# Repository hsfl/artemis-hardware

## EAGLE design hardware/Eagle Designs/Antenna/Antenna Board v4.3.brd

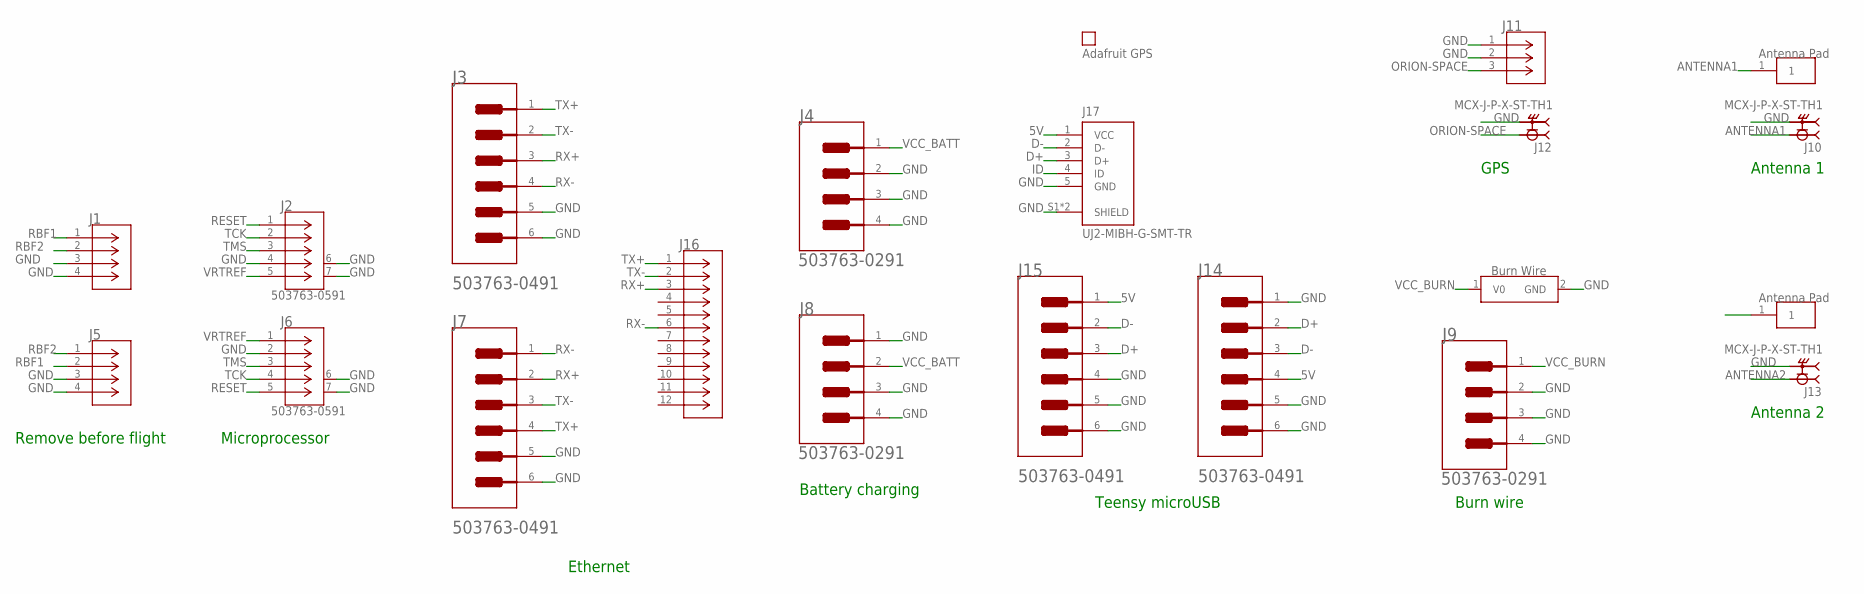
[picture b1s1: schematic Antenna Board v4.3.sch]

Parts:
GPS: PA1010D
J1, J5: 5037630291; CON_5037630291
J2, J6: 503763-0591; CONN_5037630591_MOL
J3, J7, J14, J15: MOLEX_503763-0491MOLEX_503763-0491_0_0; MOLEX_503763-0491_0
J4, J8, J9: MOLEX_503763-0291MOLEX_503763-0291_0_0; MOLEX_503763-0291_0
J10, J12, J13: MCX-J-P-X-ST-TH1; SAMTEC_MCX-J-P-X-ST-TH1
J11: U.FL-R-SMT-1(01); CONN_-SMT-1(01)
J16: ARJM11C7-104-AB-EW2; CONN_EW_ABR
J17: UJ2-MIBH-G-SMT-TR; CUI_UJ2-MIBH-G-SMT-TR
U$1, U$2: ANTENNA_PAD+HOLES
U$3: BURNWIRE

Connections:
5V: J14.4, J15.1, J17.1 (VCC)
ANTENNA1: J10.1, U$1.1
ANTENNA2: J13.1, U$2.1
D+: J14.2, J15.3, J17.3 (D+)
D-: J14.3, J15.2, J17.2 (D-)
GND: J1.3, J1.4, J2.4, J2.6, J2.7, J3.5 (MNT_1), J3.6 (MNT_2), J4.2, J4.3 (MNT_1), J4.4 (MNT_2), J5.3, J5.4, J6.2, J6.6, J6.7, J7.5 (MNT_1), J7.6 (MNT_2), J8.1, J8.3 (MNT_1), J8.4 (MNT_2), J9.2, J9.3 (MNT_1), J9.4 (MNT_2), J10.S1 (2), J10.S2 (2), J10.S3 (2), J10.S4 (2), J11.1, J11.2, J12.S1 (2), J12.S2 (2), J12.S3 (2), J12.S4 (2), J13.S1 (2), J13.S2 (2), J13.S3 (2), J13.S4 (2), J14.1, J14.5 (MNT_1), J14.6 (MNT_2), J15.4, J15.5 (MNT_1), J15.6 (MNT_2), J17.5 (GND), J17.S1 (SHIELD), J17.S2 (SHIELD), U$3.2 (GND)
ID: J17.4 (ID)
ORION-SPACE: J11.3, J12.1
RBF1: J1.1, J5.2
RBF2: J1.2, J5.1
RESET: J2.1, J6.5
RX+: J3.3, J7.2, J16.3
RX-: J3.4, J7.1, J16.6
TCK: J2.2, J6.4
TMS: J2.3, J6.3
TX+: J3.1, J7.4, J16.1
TX-: J3.2, J7.3, J16.2
VCC_BATT: J4.1, J8.2
VCC_BURN: J9.1, U$3.1 (V0)
VRTREF: J2.5, J6.1

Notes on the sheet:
Remove before flight
Microprocessor
Battery charging
Teensy microUSB
Burn wire
GPS
Antenna 1
Antenna 2
Ethernet

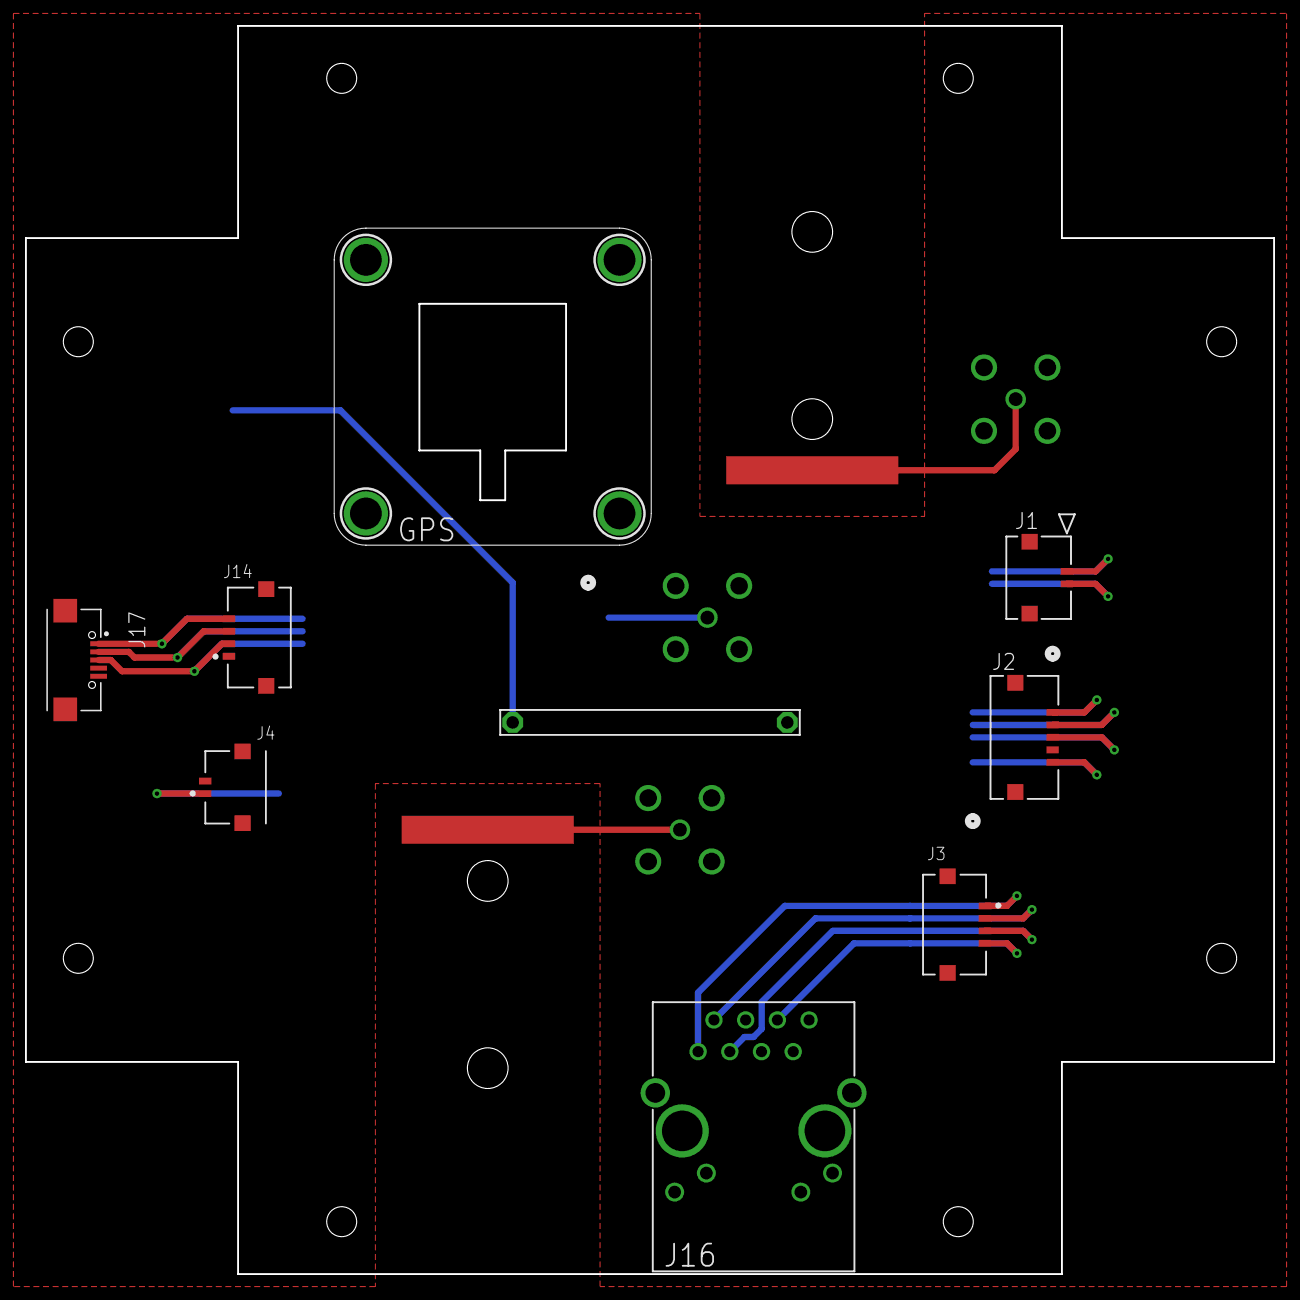
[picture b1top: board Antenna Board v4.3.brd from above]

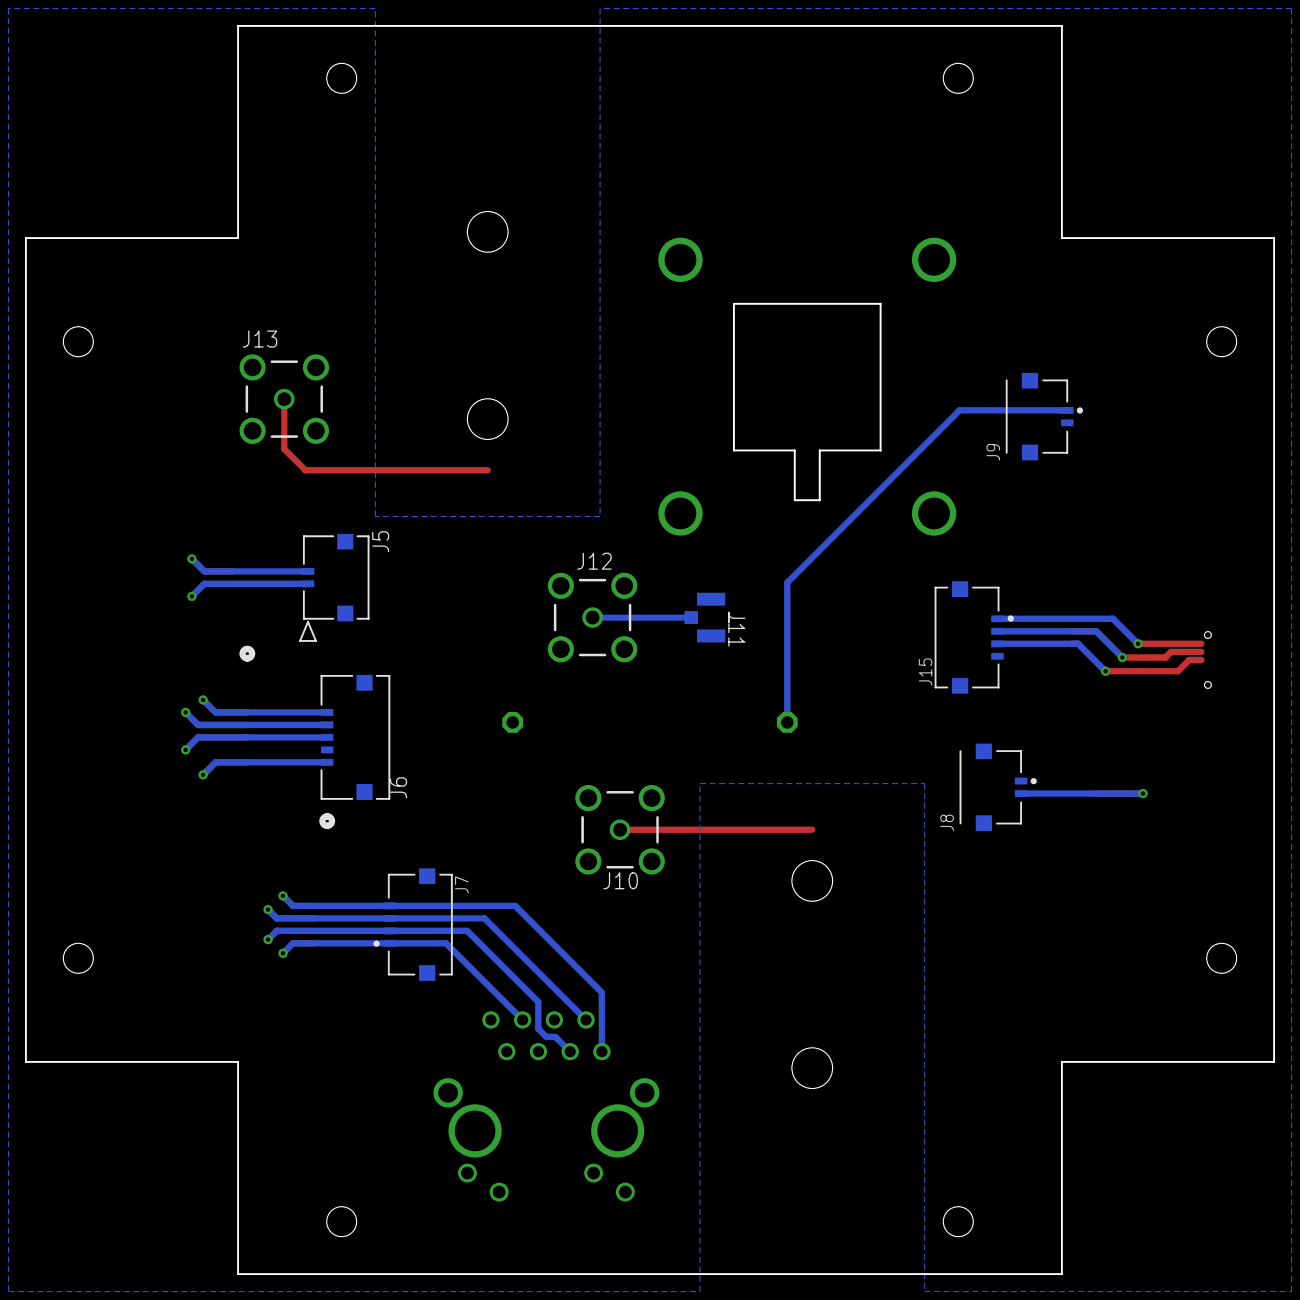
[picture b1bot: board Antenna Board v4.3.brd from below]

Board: 2 copper layers, 100.0 x 100.0 mm, 21 parts (10 on the bottom side), 19 nets.

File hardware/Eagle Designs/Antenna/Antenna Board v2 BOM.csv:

"Part";"Value";"Device";"Package";"Description";"AUTOMOTIVE";"BUILT_BY";"CENTROID_NOT_SPECIFIED";"CONN_GENDER";"CONN_ORIENTATION";"CONTACT_MATERIAL";"COPYRIGHT";"CURRENT_RATING";"DATASHEET";"DEVICE_CLASS_L1";"DEVICE_CLASS_L2";"DEVICE_CLASS_L3";"DIGIKEY_DESCRIPTION";"DIGIKEY_PART_NUMBER";"FOOTPRINT_URL";"FOOTPRINT_VARIANT_NAME_0";"HEIGHT";"LEAD_FREE";"MANUFACTURER_PART_NUMBER";"MF";"MFG_PACKAGE_IDENT";"MFG_PACKAGE_IDENT_DATE";"MFG_PACKAGE_IDENT_REV";"MOUSER_PART_NUMBER";"MPN";"NUMBER_OF_CONTACTS";"NUMBER_OF_ROWS";"PACKAGE";"PITCH";"PREFIX";"ROHS";"SOURCELIBRARY";"TEMPERATURE_RANGE_HIGH";"TEMPERATURE_RANGE_LOW";"VENDOR";"VERIFICATION_VERSION";"VOLTAGE_RATING";
"J1";"503763-0591";"503763-0591";"CONN_5037630591_MOL";"";"";"EMA_Cory";"";"";"";"";"Copyright (C) 2018 Accelerated Designs. All rights reserved";"";"https://www.molex.com/pdm_docs/sd/5037630591_sd.pdf";"";"";"";"";"";"";"";"";"";"503763-0591";"";"";"";"";"";"";"";"";"";"";"";"";"Add_to_database_2020-12-14";"";"";"Molex Connector Corporation";"";"";
"J2";"MOLEX_503763-0491MOLEX_503763-0491_0_0";"MOLEX_503763-0491MOLEX_503763-0491_0_0";"MOLEX_503763-0491_0";"Wire-To-Board Connector, Pico-Lock 503763 Series, Surface Mount, Header, 4 Contacts, 1 mm";"No";"";"No";"Male";"Right Angle";"Gold,Nickel";"";"1.5A";"https://www.molex.com/webdocs/datasheets/pdf/en-us/503763049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";"Connectors";"Headers and Wire Housings";"unset";"CONN HEADER 1MM R/A 4CKT";"WM10655CT-ND";"https://www.molex.com/pdm_docs/sd/5037630491_sd.pdf";"Recommended_Land_Pattern";"1.7mm";"Yes";"";"Molex";"503763-0491";"0";"0";"538-503763-0491";"503763-0491";"4";"1";"HDR4";"1mm";"J";"Yes";"";"+105°C";"-40°C";"";"0.0.0.1";"150V";
"J3";"MOLEX_503763-0491MOLEX_503763-0491_0_0";"MOLEX_503763-0491MOLEX_503763-0491_0_0";"MOLEX_503763-0491_0";"Wire-To-Board Connector, Pico-Lock 503763 Series, Surface Mount, Header, 4 Contacts, 1 mm";"No";"";"No";"Male";"Right Angle";"Gold,Nickel";"";"1.5A";"https://www.molex.com/webdocs/datasheets/pdf/en-us/503763049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";"Connectors";"Headers and Wire Housings";"unset";"CONN HEADER 1MM R/A 4CKT";"WM10655CT-ND";"https://www.molex.com/pdm_docs/sd/5037630491_sd.pdf";"Recommended_Land_Pattern";"1.7mm";"Yes";"";"Molex";"503763-0491";"0";"0";"538-503763-0491";"503763-0491";"4";"1";"HDR4";"1mm";"J";"Yes";"";"+105°C";"-40°C";"";"0.0.0.1";"150V";
"J4";"MOLEX_503763-0291MOLEX_503763-0291_0_0";"MOLEX_503763-0291MOLEX_503763-0291_0_0";"MOLEX_503763-0291_0";"2 Positions Header Connector 0.039" (1.00mm) Surface Mount, Right Angle Gold";"";"";"No";"";"";"";"";"";"http://www.molex.com/pdm_docs/sd/5037630291_sd.pdf";"";"";"";"CONN HEADER 1MM R/A 2CKT";"WM10654CT-ND";"";"";"";"yes";"";"Molex";"";"";"";"538-503763-0291";"503763-0291";"";"";"HDR02";"";"J";"yes";"";"+105°C";"-40°C";"";"";"";
"J5";"503763-0591";"503763-0591";"CONN_5037630591_MOL";"";"";"EMA_Cory";"";"";"";"";"Copyright (C) 2018 Accelerated Designs. All rights reserved";"";"https://www.molex.com/pdm_docs/sd/5037630591_sd.pdf";"";"";"";"";"";"";"";"";"";"503763-0591";"";"";"";"";"";"";"";"";"";"";"";"";"Add_to_database_2020-12-14";"";"";"Molex Connector Corporation";"";"";
"J6";"MOLEX_503763-0491MOLEX_503763-0491_0_0";"MOLEX_503763-0491MOLEX_503763-0491_0_0";"MOLEX_503763-0491_0";"Wire-To-Board Connector, Pico-Lock 503763 Series, Surface Mount, Header, 4 Contacts, 1 mm";"No";"";"No";"Male";"Right Angle";"Gold,Nickel";"";"1.5A";"https://www.molex.com/webdocs/datasheets/pdf/en-us/503763049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";"Connectors";"Headers and Wire Housings";"unset";"CONN HEADER 1MM R/A 4CKT";"WM10655CT-ND";"https://www.molex.com/pdm_docs/sd/5037630491_sd.pdf";"Recommended_Land_Pattern";"1.7mm";"Yes";"";"Molex";"503763-0491";"0";"0";"538-503763-0491";"503763-0491";"4";"1";"HDR4";"1mm";"J";"Yes";"";"+105°C";"-40°C";"";"0.0.0.1";"150V";
"J7";"MOLEX_503763-0491MOLEX_503763-0491_0_0";"MOLEX_503763-0491MOLEX_503763-0491_0_0";"MOLEX_503763-0491_0";"Wire-To-Board Connector, Pico-Lock 503763 Series, Surface Mount, Header, 4 Contacts, 1 mm";"No";"";"No";"Male";"Right Angle";"Gold,Nickel";"";"1.5A";"https://www.molex.com/webdocs/datasheets/pdf/en-us/503763049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";"Connectors";"Headers and Wire Housings";"unset";"CONN HEADER 1MM R/A 4CKT";"WM10655CT-ND";"https://www.molex.com/pdm_docs/sd/5037630491_sd.pdf";"Recommended_Land_Pattern";"1.7mm";"Yes";"";"Molex";"503763-0491";"0";"0";"538-503763-0491";"503763-0491";"4";"1";"HDR4";"1mm";"J";"Yes";"";"+105°C";"-40°C";"";"0.0.0.1";"150V";
"J8";"MOLEX_503763-0291MOLEX_503763-0291_0_0";"MOLEX_503763-0291MOLEX_503763-0291_0_0";"MOLEX_503763-0291_0";"2 Positions Header Connector 0.039" (1.00mm) Surface Mount, Right Angle Gold";"";"";"No";"";"";"";"";"";"http://www.molex.com/pdm_docs/sd/5037630291_sd.pdf";"";"";"";"CONN HEADER 1MM R/A 2CKT";"WM10654CT-ND";"";"";"";"yes";"";"Molex";"";"";"";"538-503763-0291";"503763-0291";"";"";"HDR02";"";"J";"yes";"";"+105°C";"-40°C";"";"";"";
"J9";"MOLEX_503763-0291MOLEX_503763-0291_0_0";"MOLEX_503763-0291MOLEX_503763-0291_0_0";"MOLEX_503763-0291_0";"2 Positions Header Connector 0.039" (1.00mm) Surface Mount, Right Angle Gold";"";"";"No";"";"";"";"";"";"http://www.molex.com/pdm_docs/sd/5037630291_sd.pdf";"";"";"";"CONN HEADER 1MM R/A 2CKT";"WM10654CT-ND";"";"";"";"yes";"";"Molex";"";"";"";"538-503763-0291";"503763-0291";"";"";"HDR02";"";"J";"yes";"";"+105°C";"-40°C";"";"";"";
"J10";"U.FL-R-SMT-1(01)";"U.FL-R-SMT-1(01)";"CONN_-SMT-1(01)";"";"";"EMA_Matt";"";"";"";"";"Copyright (C) 2018 Accelerated Designs. All rights reserved";"";"";"";"";"";"";"";"";"";"";"";"U.FL-R-SMT-1(01)";"";"";"";"";"";"";"";"";"";"";"";"";"Hirose_12_20_2019";"";"";"Hirose";"";"";
"J11";"U.FL-R-SMT-1(01)";"U.FL-R-SMT-1(01)";"CONN_-SMT-1(01)";"";"";"EMA_Matt";"";"";"";"";"Copyright (C) 2018 Accelerated Designs. All rights reserved";"";"";"";"";"";"";"";"";"";"";"";"U.FL-R-SMT-1(01)";"";"";"";"";"";"";"";"";"";"";"";"";"Hirose_12_20_2019";"";"";"Hirose";"";"";
"J12";"U.FL-R-SMT-1(01)";"U.FL-R-SMT-1(01)";"CONN_-SMT-1(01)";"";"";"EMA_Matt";"";"";"";"";"Copyright (C) 2018 Accelerated Designs. All rights reserved";"";"";"";"";"";"";"";"";"";"";"";"U.FL-R-SMT-1(01)";"";"";"";"";"";"";"";"";"";"";"";"";"Hirose_12_20_2019";"";"";"Hirose";"";"";
"U$2";"ANTENNA_PAD";"ANTENNA_PAD";"ANTENNA_PAD";"";"";"";"";"";"";"";"";"";"";"";"";"";"";"";"";"";"";"";"";"";"";"";"";"";"";"";"";"";"";"";"";"";"";"";"";"";"";
"U$3";"BURNWIRE";"BURNWIRE";"BURNWIRE";"";"";"";"";"";"";"";"";"";"";"";"";"";"";"";"";"";"";"";"";"";"";"";"";"";"";"";"";"";"";"";"";"";"";"";"";"";"";

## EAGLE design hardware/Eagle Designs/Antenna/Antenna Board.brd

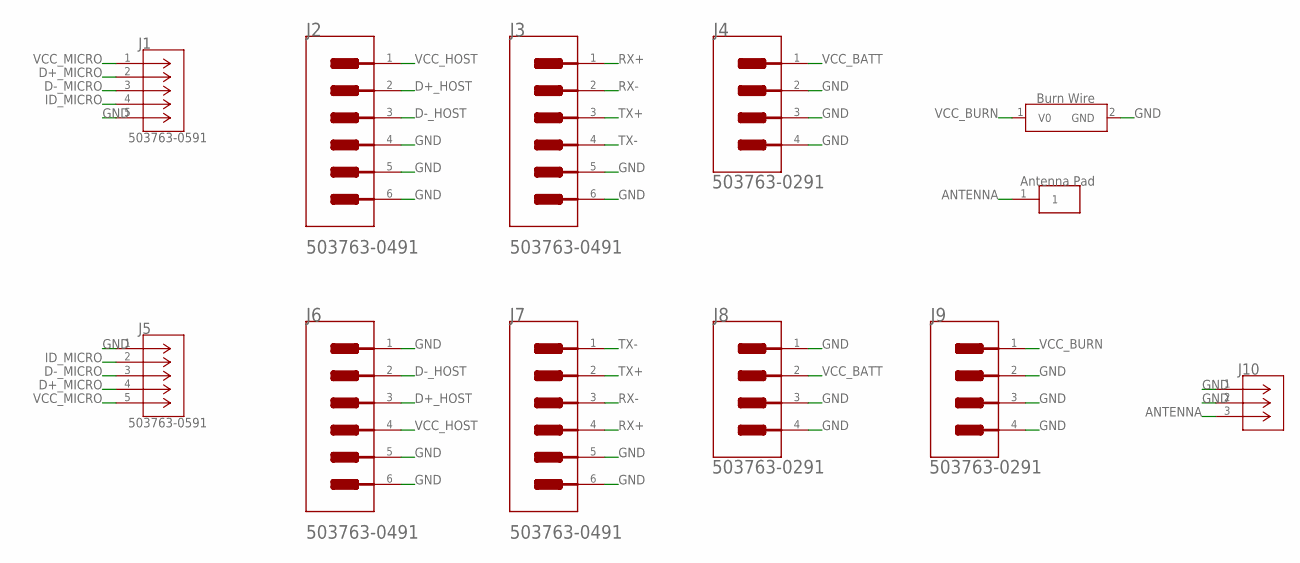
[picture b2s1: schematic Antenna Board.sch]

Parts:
J1, J5: 503763-0591; CONN_5037630591_MOL
J2, J3, J6, J7: MOLEX_503763-0491MOLEX_503763-0491_0_0; MOLEX_503763-0491_0
J4, J8, J9: MOLEX_503763-0291MOLEX_503763-0291_0_0; MOLEX_503763-0291_0
J10: U.FL-R-SMT-1(01); CONN_-SMT-1(01)
U$2: ANTENNA_PAD
U$3: BURNWIRE

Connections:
ANTENNA: J10.3, U$2.1
D+_HOST: J2.2, J6.3
D+_MICRO: J1.2, J5.4
D-_HOST: J2.3, J6.2
D-_MICRO: J1.3, J5.3
GND: J1.5, J2.4, J2.5 (MNT_1), J2.6 (MNT_2), J3.5 (MNT_1), J3.6 (MNT_2), J4.2, J4.3 (MNT_1), J4.4 (MNT_2), J5.1, J6.1, J6.5 (MNT_1), J6.6 (MNT_2), J7.5 (MNT_1), J7.6 (MNT_2), J8.1, J8.3 (MNT_1), J8.4 (MNT_2), J9.2, J9.3 (MNT_1), J9.4 (MNT_2), J10.1, J10.2, U$3.2 (GND)
ID_MICRO: J1.4, J5.2
RX+: J3.1, J7.4
RX-: J3.2, J7.3
TX+: J3.3, J7.2
TX-: J3.4, J7.1
VCC_BATT: J4.1, J8.2
VCC_BURN: J9.1, U$3.1 (V0)
VCC_HOST: J2.1, J6.4
VCC_MICRO: J1.1, J5.5

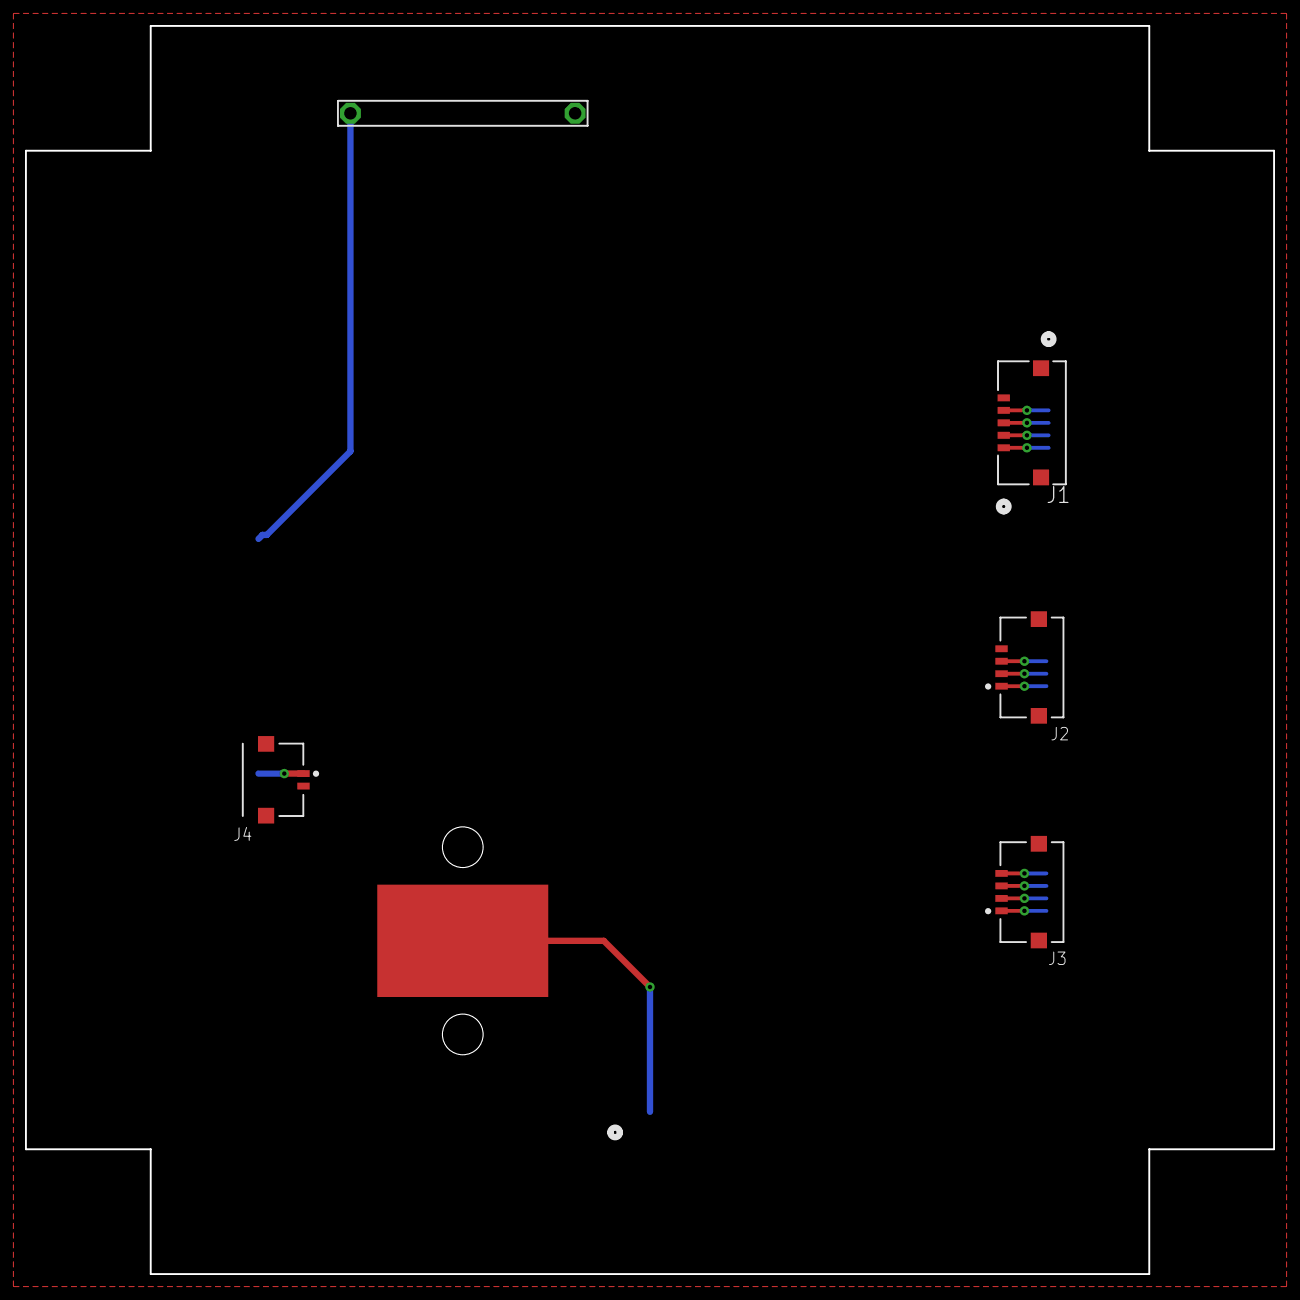
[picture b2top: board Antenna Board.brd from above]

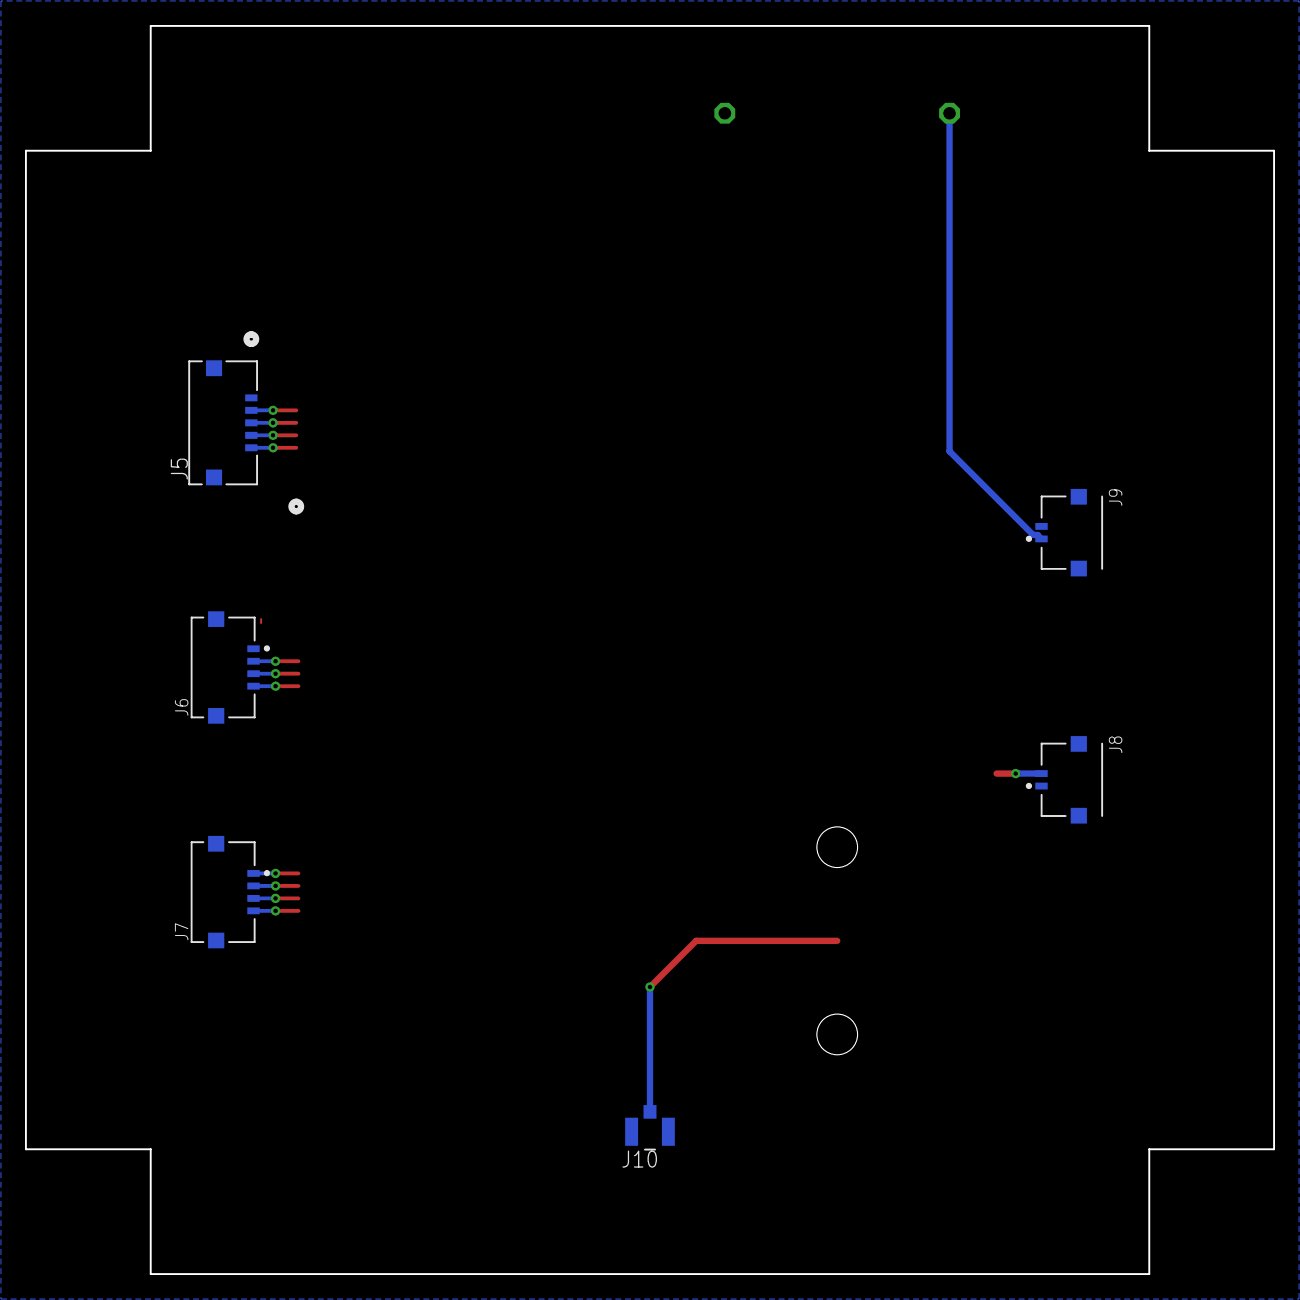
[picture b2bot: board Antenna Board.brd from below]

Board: 2 copper layers, 100.0 x 100.0 mm, 12 parts (6 on the bottom side), 15 nets.

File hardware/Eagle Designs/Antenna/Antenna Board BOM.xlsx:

Part | Value | Device | Package | Description
J1, J5 | 503763-0591 | 503763-0591 | CONN_5037630591_MOL
J2, J3, J6, J7 | 503763-0491 | MOLEX_503763-0491MOLEX_503763-0491_0_0 | MOLEX_503763-0491_0 | Wire-To-Board Connector, Pico-Lock 503763 Series, Surface Mount, Header, 4 Cont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
J4, J8, J9 | 503763-0291 | MOLEX_503763-0291MOLEX_503763-0291_0_0 | MOLEX_503763-0291_0 | 2 Positions Header Connector 0.039 (1.00mm) Surface Mount, Right Angle Gold"
J10 | U.FL-R-SMT-1(01) | U.FL-R-SMT-1(01) | CONN_-SMT-1(01)
U$2 | ANTENNA_PAD | ANTENNA_PAD | ANTENNA_PAD
U$3 | BURNWIRE | BURNWIRE | BURNWIRE

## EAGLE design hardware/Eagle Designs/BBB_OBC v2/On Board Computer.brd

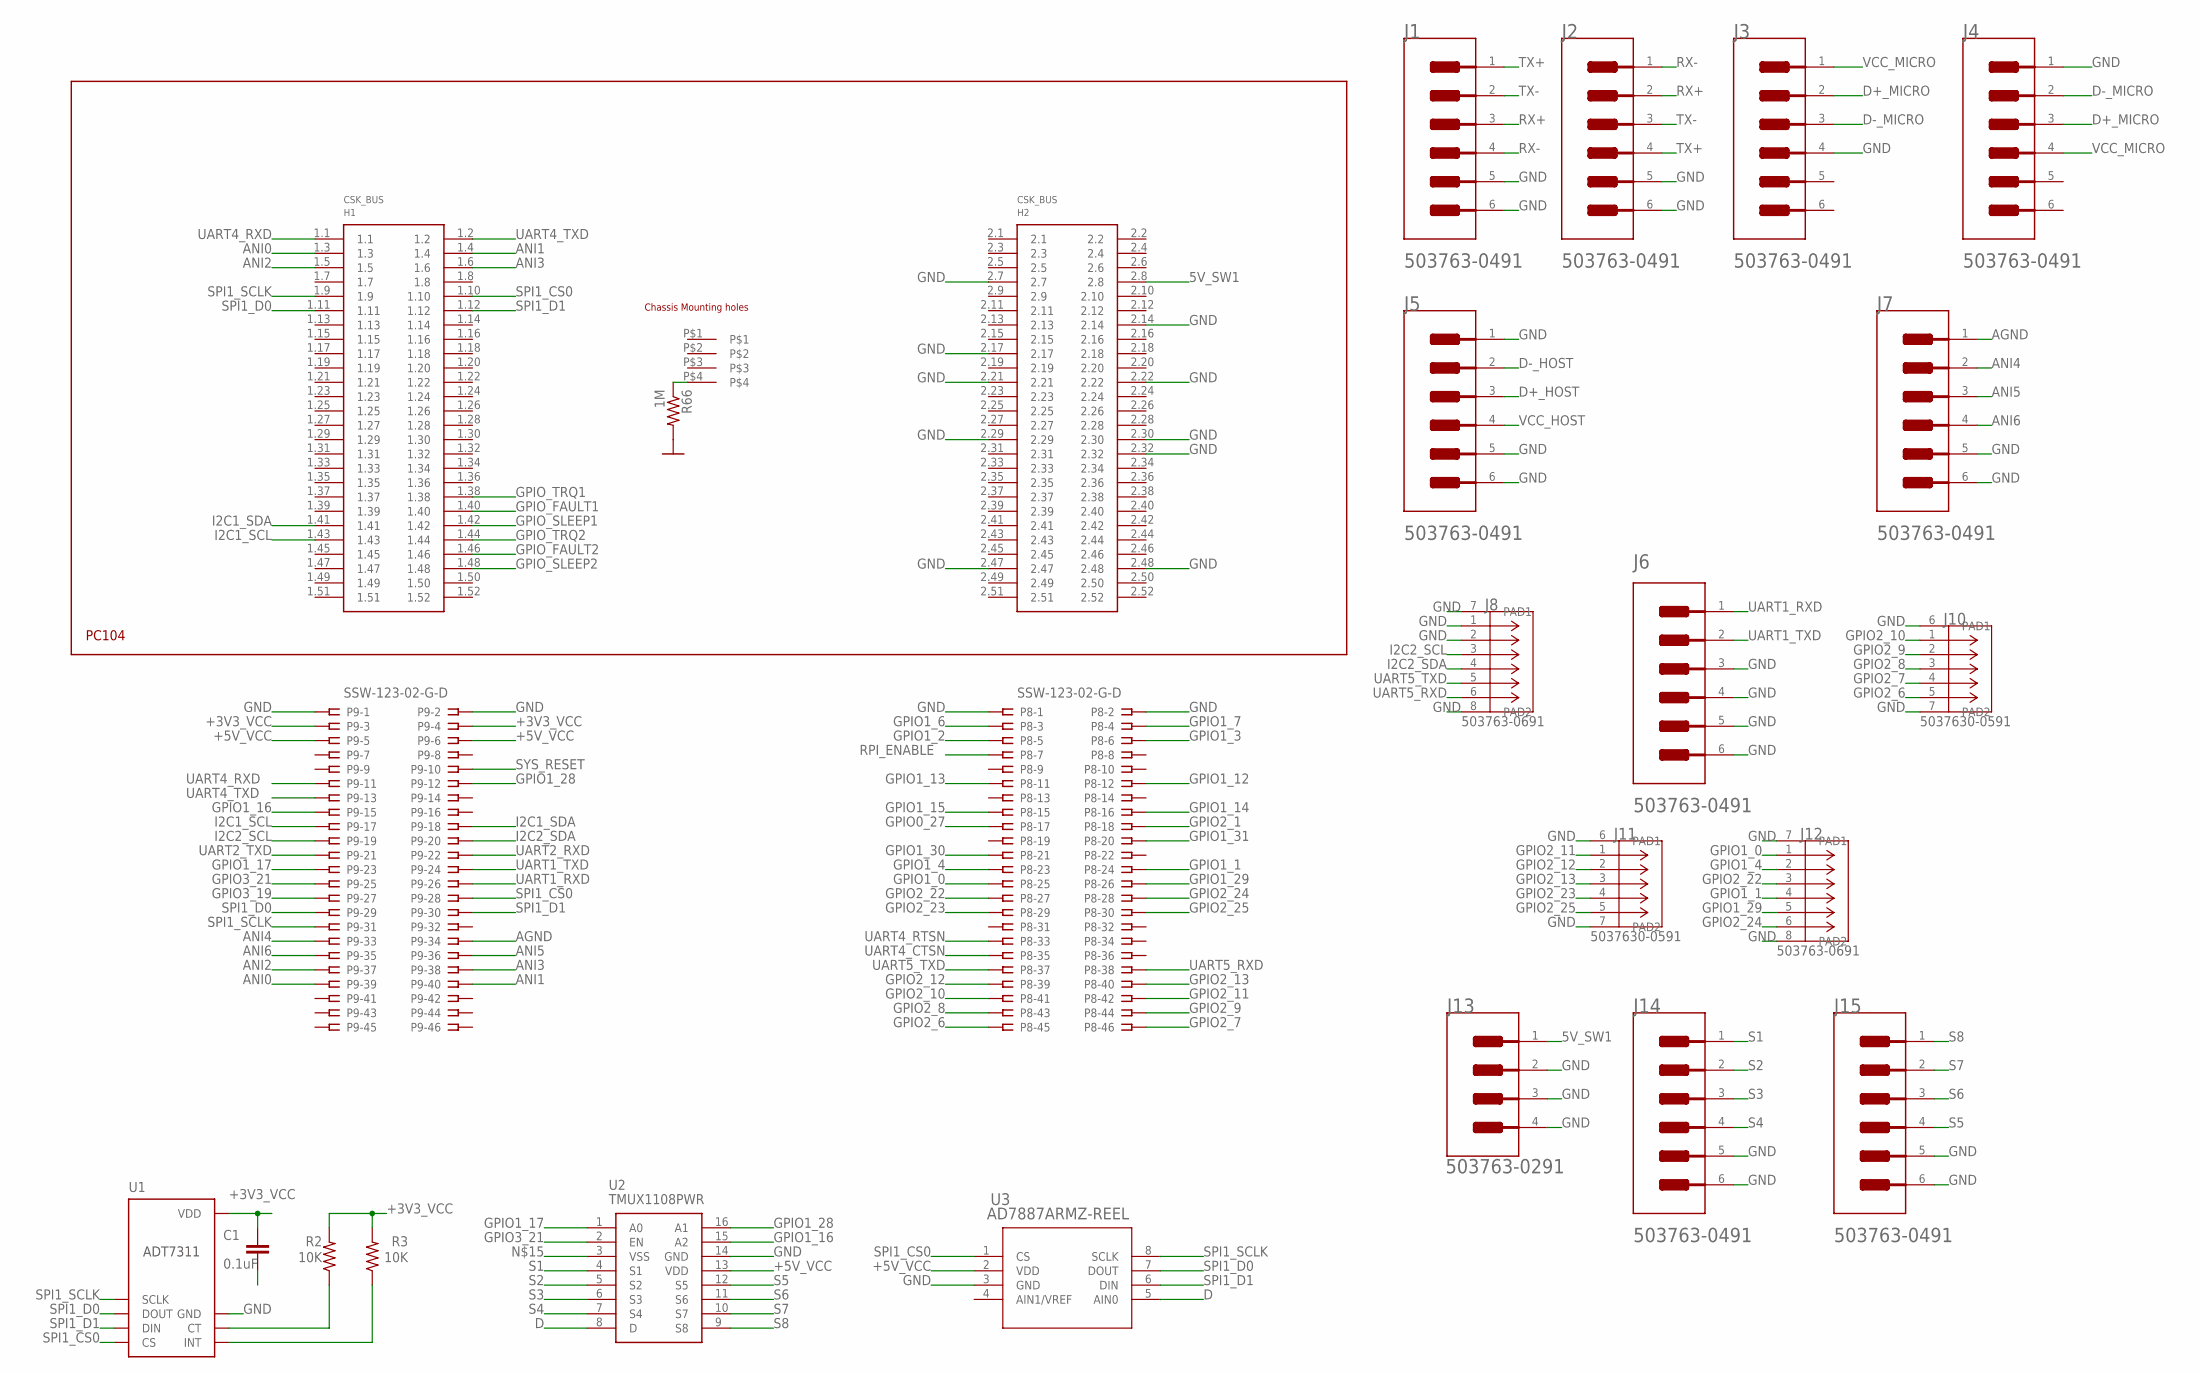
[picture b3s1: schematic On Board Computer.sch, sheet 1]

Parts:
C1: 0.1uF; 0805
H1: PC104_WCONN
J1, J2, J3, J4, J5, J6, J7, J14, J15: MOLEX_503763-0491MOLEX_503763-0491_0_0; MOLEX_503763-0491_0
J8, J12: 503763-0691; CONN_503763-0691_MOL
J10, J11: 503763-0591; CONN_5037630591_MOL
J13: MOLEX_503763-0291MOLEX_503763-0291_0_0; MOLEX_503763-0291_0
P8, P9: SSW-123-02-G-D
R2, R3: 10K; 0805
R66: 1M; 0805
U1: ADT7311; SOIC-8
U2: TMUX1108PWR; SOP65P640X120-16N
U3: AD7887ARMZ-REEL; RM_8_ADI

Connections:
5V_SW1: H1.2.8, J13.1; also elsewhere on the board
+3V3_VCC: C1.1, P9.3, P9.4, R2.2, R3.2, U1.8 (VDD); also elsewhere on the board
+5V_VCC: P9.5, P9.6, U2.13 (VDD), U3.2 (VDD)
AGND: J7.1, P9.34
ANI0: H1.1.3, P9.39
ANI1: H1.1.4, P9.40
ANI2: H1.1.5, P9.37
ANI3: H1.1.6, P9.38
ANI4: J7.2, P9.33
ANI5: J7.3, P9.36
ANI6: J7.4, P9.35
D: U2.8 (D), U3.5 (AIN0)
D+_HOST: J5.3; also elsewhere on the board
D+_MICRO: J3.2, J4.3
D-_HOST: J5.2; also elsewhere on the board
D-_MICRO: J3.3, J4.2
GND: C1.2, H1.2.7, H1.2.14, H1.2.17, H1.2.21, H1.2.22, H1.2.29, H1.2.30, H1.2.32, H1.2.47, H1.2.48, J1.5 (MNT_1), J1.6 (MNT_2), J2.5 (MNT_1), J2.6 (MNT_2), J3.4, J4.1, J5.1, J5.5 (MNT_1), J5.6 (MNT_2), J6.3, J6.4, J6.5 (MNT_1), J6.6 (MNT_2), J7.5 (MNT_1), J7.6 (MNT_2), J8.1, J8.2, J8.7 (PAD1), J8.8 (PAD2), J10.6 (PAD1), J10.7 (PAD2), J11.6 (PAD1), J11.7 (PAD2), J12.7 (PAD1), J12.8 (PAD2), J13.2, J13.3 (MNT_1), J13.4 (MNT_2), J14.5 (MNT_1), J14.6 (MNT_2), J15.5 (MNT_1), J15.6 (MNT_2), P8.1, P8.2, P9.1, P9.2, R66.2, U1.7 (GND), U2.14 (GND), U3.3 (GND); also elsewhere on the board
GPIO0_27: P8.17
GPIO1_0: J12.1, P8.25
GPIO1_1: J12.4, P8.24
GPIO1_2: P8.5
GPIO1_3: P8.6
GPIO1_4: J12.2, P8.23
GPIO1_6: P8.3
GPIO1_7: P8.4
GPIO1_12: P8.12
GPIO1_13: P8.11
GPIO1_14: P8.16
GPIO1_15: P8.15
GPIO1_16: P9.15, U2.15 (A2)
GPIO1_17: P9.23, U2.1 (A0)
GPIO1_28: P9.12, U2.16 (A1)
GPIO1_29: J12.5, P8.26
GPIO1_30: P8.21
GPIO1_31: P8.20
GPIO2_1: P8.18
GPIO2_6: J10.5, P8.45
GPIO2_7: J10.4, P8.46
GPIO2_8: J10.3, P8.43
GPIO2_9: J10.2, P8.44
GPIO2_10: J10.1, P8.41
GPIO2_11: J11.1, P8.42
GPIO2_12: J11.2, P8.39
GPIO2_13: J11.3, P8.40
GPIO2_22: J12.3, P8.27
GPIO2_23: J11.4, P8.29
GPIO2_24: J12.6, P8.28
GPIO2_25: J11.5, P8.30
GPIO3_19: P9.27
GPIO3_21: P9.25, U2.2 (EN)
GPIO_FAULT1: H1.1.40
GPIO_FAULT2: H1.1.46
GPIO_SLEEP1: H1.1.42
GPIO_SLEEP2: H1.1.48
GPIO_TRQ1: H1.1.38
GPIO_TRQ2: H1.1.44
I2C1_SCL: H1.1.43, P9.17
I2C1_SDA: H1.1.41, P9.18
I2C2_SCL: J8.3, P9.19
I2C2_SDA: J8.4, P9.20
unnamed: H1.P$4, R66.1
RPI_ENABLE: P8.7; also elsewhere on the board
RX+: J1.3, J2.2
RX-: J1.4, J2.1
S1: J14.1, U2.4 (S1)
S2: J14.2, U2.5 (S2)
S3: J14.3, U2.6 (S3)
S4: J14.4, U2.7 (S4)
S5: J15.4, U2.12 (S5)
S6: J15.3, U2.11 (S6)
S7: J15.2, U2.10 (S7)
S8: J15.1, U2.9 (S8)
SPI1_CS0: H1.1.10, P9.28, U1.4 (CS), U3.1 (CS)
SPI1_D0: H1.1.11, P9.29, U1.2 (DOUT), U3.7 (DOUT)
SPI1_D1: H1.1.12, P9.30, U1.3 (DIN), U3.6 (DIN)
SPI1_SCLK: H1.1.9, P9.31, U1.1 (SCLK), U3.8 (SCLK)
SYS_RESET: P9.10
TX+: J1.1, J2.4
TX-: J1.2, J2.3
U11_CT: R2.1, U1.6 (CT)
U11_INT: R3.1, U1.5 (INT)
UART1_RXD: J6.1, P9.26
UART1_TXD: J6.2, P9.24
UART2_RXD: P9.22; also elsewhere on the board
UART2_TXD: P9.21; also elsewhere on the board
UART4_CTSN: P8.35
UART4_RTSN: P8.33
UART4_RXD: H1.1.1, P9.11
UART4_TXD: H1.1.2, P9.13
UART5_RXD: J8.6, P8.38
UART5_TXD: J8.5, P8.37
VCC_HOST: J5.4; also elsewhere on the board
VCC_MICRO: J3.1, J4.4

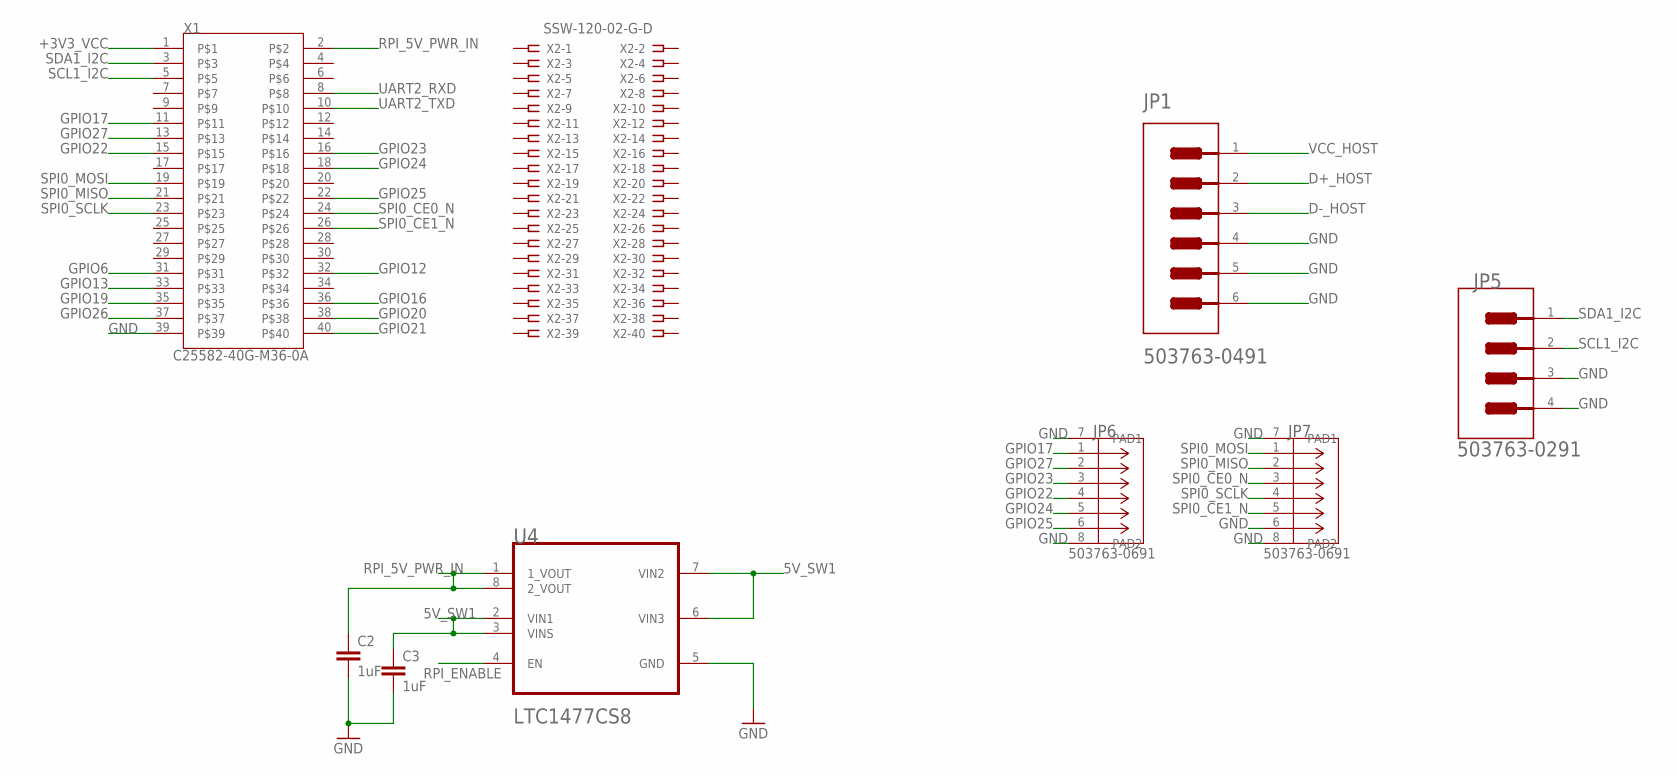
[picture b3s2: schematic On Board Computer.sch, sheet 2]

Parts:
C2, C3: 1uF; 0805
JP1: MOLEX_503763-0491MOLEX_503763-0491_0_0; MOLEX_503763-0491_0
JP5: MOLEX_503763-0291MOLEX_503763-0291_0_0; MOLEX_503763-0291_0
JP6, JP7: 503763-0691; CONN_503763-0691_MOL
U4: LTC1477CS8LINEAR_TECHNOLOGY_LTC1477CS8_0_2; LINEAR_TECHNOLOGY_LTC1477CS8_2
X1: C25582-40G-M36-0A; ADAFRUIT_C25582-40G-M36-0A_0
X2: SSW-120-02-G-D

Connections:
5V_SW1: C3.1, U4.2 (VIN1), U4.3 (VINS), U4.6 (VIN3), U4.7 (VIN2); also elsewhere on the board
+3V3_VCC: X1.1; also elsewhere on the board
D+_HOST: JP1.2; also elsewhere on the board
D-_HOST: JP1.3; also elsewhere on the board
GND: C2.2, C3.2, JP1.4, JP1.5 (MNT_1), JP1.6 (MNT_2), JP5.3 (MNT_1), JP5.4 (MNT_2), JP6.7 (PAD1), JP6.8 (PAD2), JP7.6, JP7.7 (PAD1), JP7.8 (PAD2), U4.5 (GND), X1.39; also elsewhere on the board
GPIO6: X1.31
GPIO12: X1.32
GPIO13: X1.33
GPIO16: X1.36
GPIO17: JP6.1, X1.11
GPIO19: X1.35
GPIO20: X1.38
GPIO21: X1.40
GPIO22: JP6.4, X1.15
GPIO23: JP6.3, X1.16
GPIO24: JP6.5, X1.18
GPIO25: JP6.6, X1.22
GPIO26: X1.37
GPIO27: JP6.2, X1.13
RPI_5V_PWR_IN: C2.1, U4.1 (1_VOUT), U4.8 (2_VOUT), X1.2
RPI_ENABLE: U4.4 (EN); also elsewhere on the board
SCL1_I2C: JP5.2, X1.5
SDA1_I2C: JP5.1, X1.3
SPI0_CE0_N: JP7.3, X1.24
SPI0_CE1_N: JP7.5, X1.26
SPI0_MISO: JP7.2, X1.21
SPI0_MOSI: JP7.1, X1.19
SPI0_SCLK: JP7.4, X1.23
UART2_RXD: X1.8; also elsewhere on the board
UART2_TXD: X1.10; also elsewhere on the board
VCC_HOST: JP1.1; also elsewhere on the board

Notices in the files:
parts and their libraries:
Molex_503763-0291: COPYRIGHT: Copyright (C) 2018 Accelerated Designs. All rights reserved
SparkFun-PowerSymbols: Licensing: Creative Commons ShareAlike 4.0 International - https://creativecommons.org/licenses/by-sa/4.0
TMP36FSZR_8: COPYRIGHT: Copyright (C) 2021 Ultra Librarian. All rights reserved.
